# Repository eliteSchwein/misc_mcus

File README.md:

# Monteurszimmer-Door-Hardware

## Getting started

Requires KiCad knowledge and global easyeda2kicad

## Add LCSC File
```shell
easyeda2kicad --full --lcsc_id=C12074 --output ./Library/easyeda2kicad/ 
bash migrateLibrary.sh #Linux
migrateLibrary.bat #Windows (untested, i use linux not windows)
```

## Links

symbol

${KIPRJMOD}/../../library/easyeda2kicad/.kicad_sym

footprint

${KIPRJMOD}/../../library/easyeda2kicad/.pretty
${KIPRJMOD}/../library/selfmadestuff/Library.pretty

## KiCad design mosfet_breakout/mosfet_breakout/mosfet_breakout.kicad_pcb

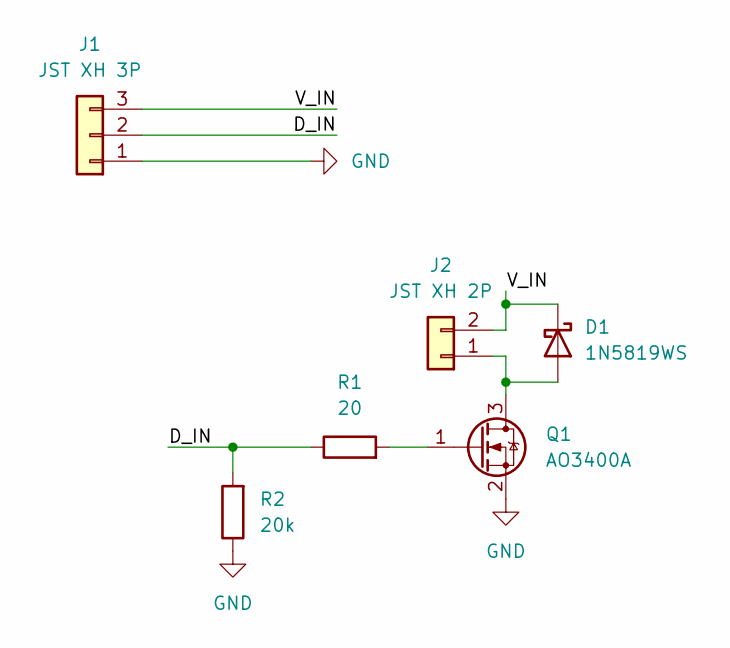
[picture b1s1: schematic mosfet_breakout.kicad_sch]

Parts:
D1: 1N5819WS; D_SOD-323
J1: JST XH 3P; JST_XH_B3B-XH-A_1x03_P2.50mm_Vertical
J2: JST XH 2P; JST_XH_B2B-XH-A_1x02_P2.50mm_Vertical
Q1: AO3400A; SOT-23
R1: 20; R_0603_1608Metric
R2: 20k; R_0603_1608Metric

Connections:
/D_IN: J1.2, R1.1, R2.2
/V_IN: D1.1 (K), J1.3, J2.2
GND: J1.1, Q1.2 (S), R2.1
unnamed: D1.2 (A), J2.1, Q1.3 (D)
unnamed: Q1.1 (G), R1.2

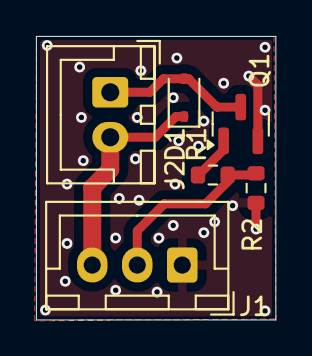
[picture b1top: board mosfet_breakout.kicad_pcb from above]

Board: 2 copper layers, 13.3 x 15.8 mm, 6 parts (0 on the bottom side), 5 nets.

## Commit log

2025-04-26 initial upload
2025-04-26 feat: add initial klp expander
2025-04-27 update schematics
2025-04-28 feat: merge middle mcu into klp expander. both projects will be merged and will get a new name
